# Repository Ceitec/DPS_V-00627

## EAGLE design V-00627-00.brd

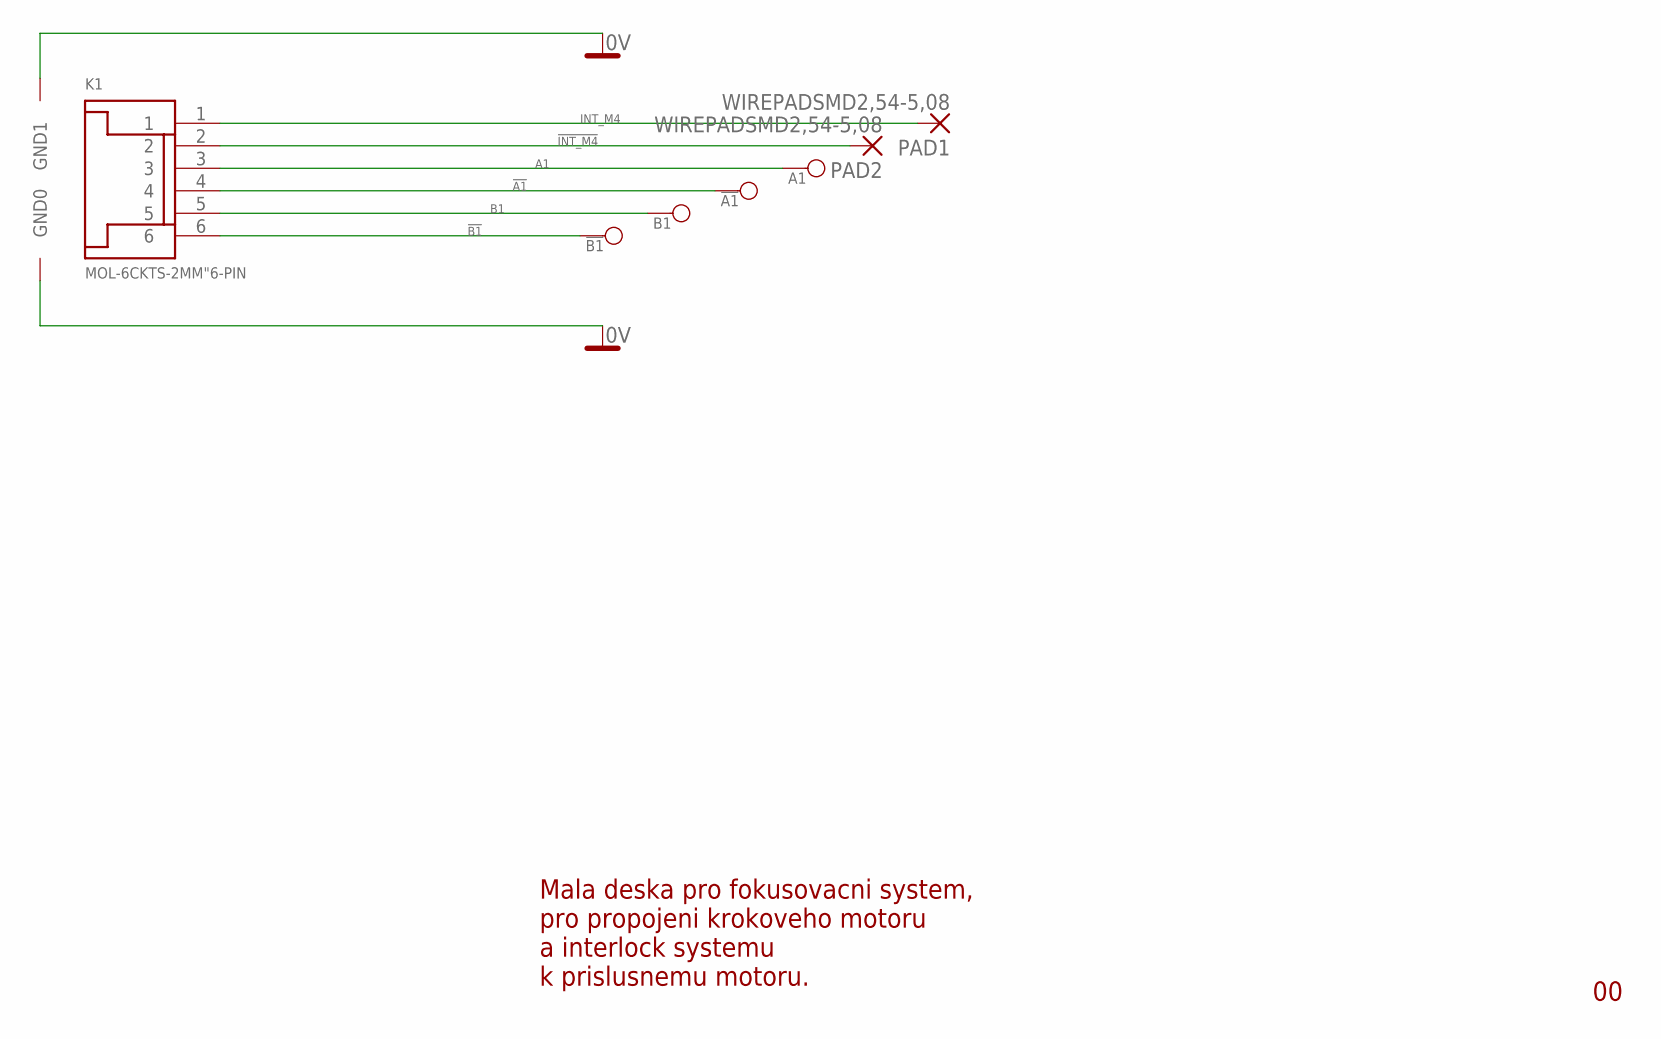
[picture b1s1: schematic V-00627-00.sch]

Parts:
!A1: PAD_1
!B1: PAD_1
A1: PAD_1
B1: PAD_1
K1: MOL-6CKTS-2MM"6-PIN; 6CKTS
PAD1, PAD2: WIREPADSMD2,54-5,08; SMD2,54-5,08

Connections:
0V: K1.GND0, K1.GND1
!A1: !A1.1, K1.4
!B1: !B1.1, K1.6
!INT_M4: K1.2, PAD2.1
A1: A1.1, K1.3
B1: B1.1, K1.5
INT_M4: K1.1, PAD1.1

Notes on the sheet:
Mala deska pro fokusovacni system, pro propojeni krokoveho motoru a interlock systemu k prislusnemu motoru.

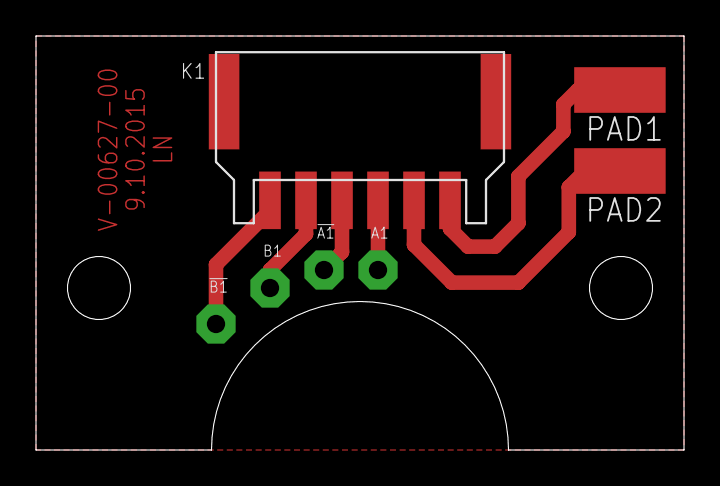
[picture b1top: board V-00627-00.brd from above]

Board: 2 copper layers, 36.0 x 23.0 mm, 7 parts (0 on the bottom side), 7 nets.

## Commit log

2015-11-10 :boom::camel: Added .gitattributes & .gitignore files
2015-11-10 Prvotní verze

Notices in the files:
parts and their libraries:
Copyright (C) PaJa 2001-2014
